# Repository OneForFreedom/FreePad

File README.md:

# This is FreePad.
The revolutonary pad with a 3x5 key matrix layout incorporating 3 rotary encoders!

This is a fully wireless system with a built in Battery! It features a nice!nano as it's main mcu!

I made this because I thought havigng a wireless pad would be really fun to have.

# Juicy Images!
.png)  
.png)  
.png)  
.png)  

# And the BEAUTIFUL BOM!

| Item                 | Price (£) | Price (\$) | Link                                                                           |
| -------------------- | --------- | ---------- | ------------------------------------------------------------------------------ |
| Keycaps              | 3.45      | 4.62       | [Link](https://www.aliexpress.com/item/1005006005905021.html)                  |
| Switches             | 2.59      | 3.47       | [Link](https://www.aliexpress.com/item/1005006578935785.html)                  |
| Nice Nano            | 2.27      | 3.04       | [Link](https://www.aliexpress.com/item/1005001621678794.html)                  |
| Rotary Encoders      | 1.92      | 2.57       | [Link](https://www.aliexpress.com/item/33014968983.html)                       |
| Rotary Encoder Caps  | 1.06      | 1.42       | [Link](https://www.aliexpress.com/item/1005005983134515.html)                  |
| USB-C Cable          | 0.61      | 0.82       | [Link](https://www.aliexpress.com/item/33014968983.html)                       |
| Felt Pads            | 1.95      | 2.61       | [Link](https://www.aliexpress.com/item/1005002289117326.html)                  |
| O Rings              | 1.50      | 2.01       | [Link](https://www.aliexpress.com/item/1005005950575947.html)                  |
| Battery              | 6.39      | 8.56       | [Link](https://www.amazon.co.uk/gp/product/B0C7462TMS?smid=ASLRAS85RTYN3&th=1) |
| 3D Printing Shipping | 3.35      | 4.49       | [Link](https://send.royalmail.com/?iid=RM0624_NAV_SEND)                        |
| PCB                  | 7.94      | 10.64      | [Link](https://jlcpcb.com/)                                                    |
|                      |           |            |                                                                                |
| **Grand Total**      | **33.03** | **44.28**  |                                                                                |

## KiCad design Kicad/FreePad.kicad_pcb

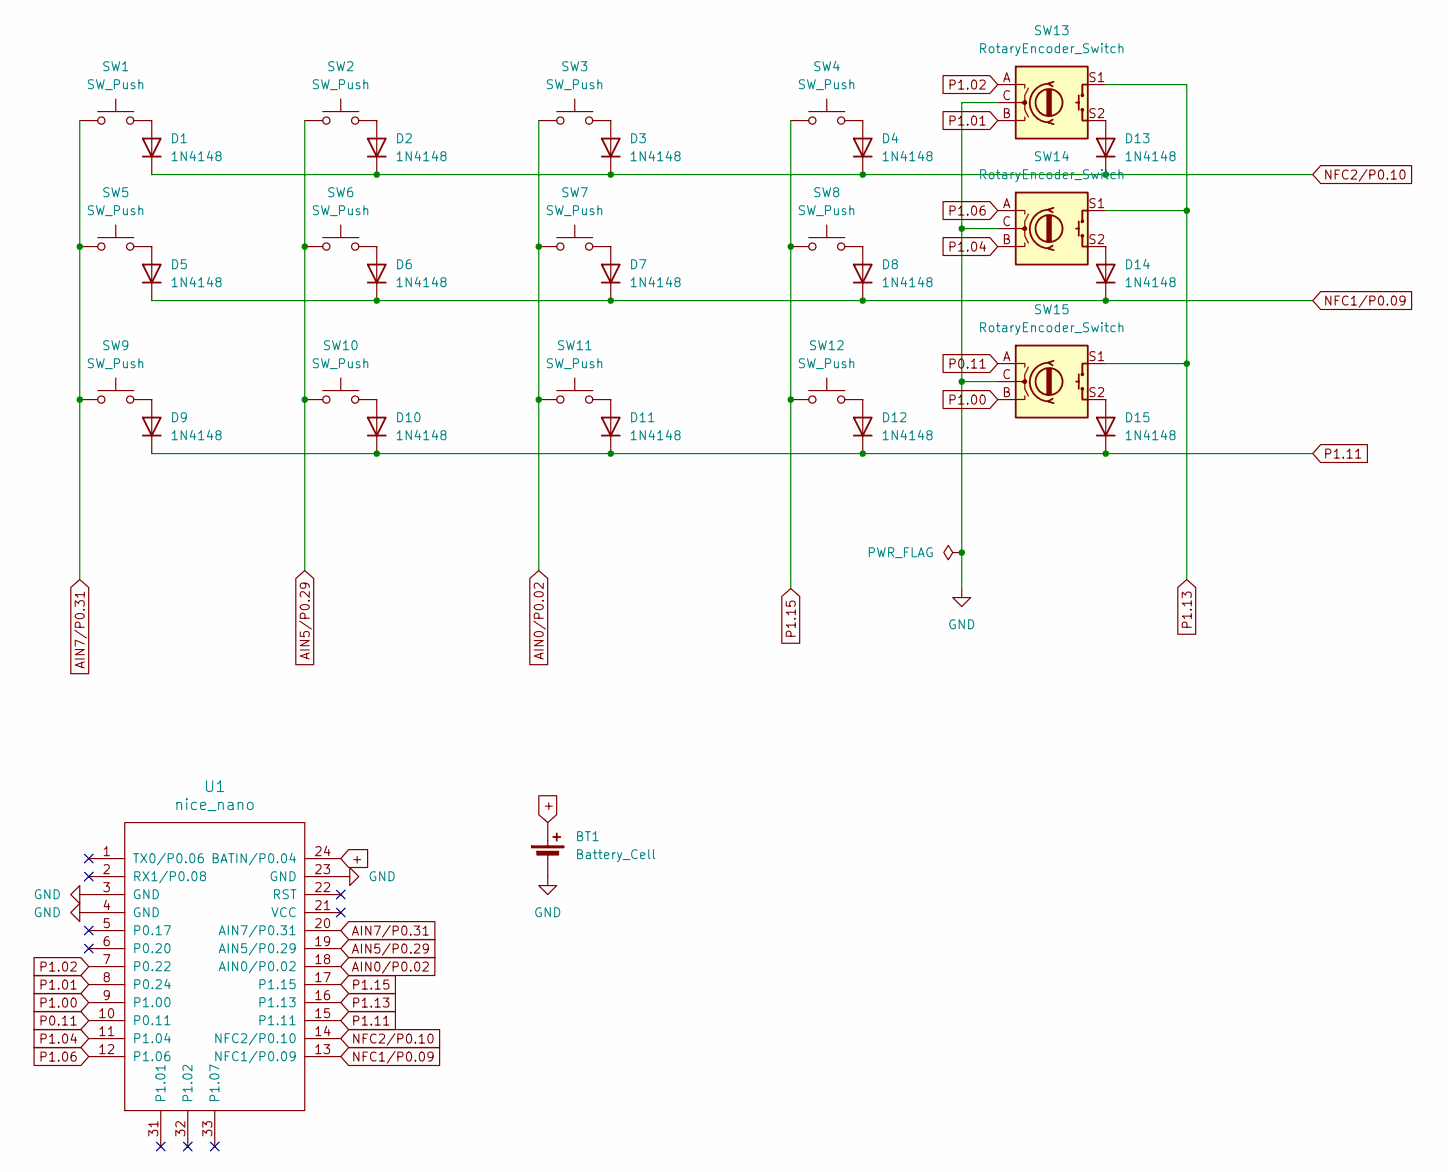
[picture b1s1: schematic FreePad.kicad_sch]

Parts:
BT1: Battery_Cell
D1, D2, D3, D4, D5, D6, D7, D8, D9, D10, D11, D12, D13, D14, D15: 1N4148; D_DO-35_SOD27_P7.62mm_Horizontal
SW1, SW2, SW3, SW4, SW5, SW6, SW7, SW8, SW9, SW10, SW11, SW12: SW_Push; SW_Cherry_MX_1.00u_PCB
SW13, SW14, SW15: RotaryEncoder_Switch; RotaryEncoder_Alps_EC11E-Switch_Vertical_H20mm_MountingHoles
U1: nice_nano

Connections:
+: BT1.1 (+), U1.24 (BATIN/P0.04)
AIN0/P0.02: SW3.1, SW7.1, SW11.1, U1.18 (AIN0/P0.02)
AIN5/P0.29: SW2.1, SW6.1, SW10.1, U1.19 (AIN5/P0.29)
AIN7/P0.31: SW1.1, SW5.1, SW9.1, U1.20 (AIN7/P0.31)
GND: BT1.2 (-), SW13.C, SW14.C, SW15.C, U1.3 (GND), U1.4 (GND), U1.23 (GND)
NFC1/P0.09: D5.1 (K), D6.1 (K), D7.1 (K), D8.1 (K), D14.1 (K), U1.13 (NFC1/P0.09)
NFC2/P0.10: D1.1 (K), D2.1 (K), D3.1 (K), D4.1 (K), D13.1 (K), U1.14 (NFC2/P0.10)
unnamed: D1.2 (A), SW1.2
unnamed: D2.2 (A), SW2.2
unnamed: D3.2 (A), SW3.2
unnamed: D4.2 (A), SW4.2
unnamed: D5.2 (A), SW5.2
unnamed: D6.2 (A), SW6.2
unnamed: D7.2 (A), SW7.2
unnamed: D8.2 (A), SW8.2
unnamed: D9.2 (A), SW9.2
unnamed: D10.2 (A), SW10.2
unnamed: D11.2 (A), SW11.2
unnamed: D12.2 (A), SW12.2
unnamed: D13.2 (A), SW13.S2
unnamed: D14.2 (A), SW14.S2
unnamed: D15.2 (A), SW15.S2
P0.11: SW15.A, U1.10 (P0.11)
P1.00: SW15.B, U1.9 (P1.00)
P1.01: SW13.B, U1.8 (P0.24)
P1.02: SW13.A, U1.7 (P0.22)
P1.04: SW14.B, U1.11 (P1.04)
P1.06: SW14.A, U1.12 (P1.06)
P1.11: D9.1 (K), D10.1 (K), D11.1 (K), D12.1 (K), D15.1 (K), U1.15 (P1.11)
P1.13: SW13.S1, SW14.S1, SW15.S1, U1.16 (P1.13)
P1.15: SW4.1, SW8.1, SW12.1, U1.17 (P1.15)

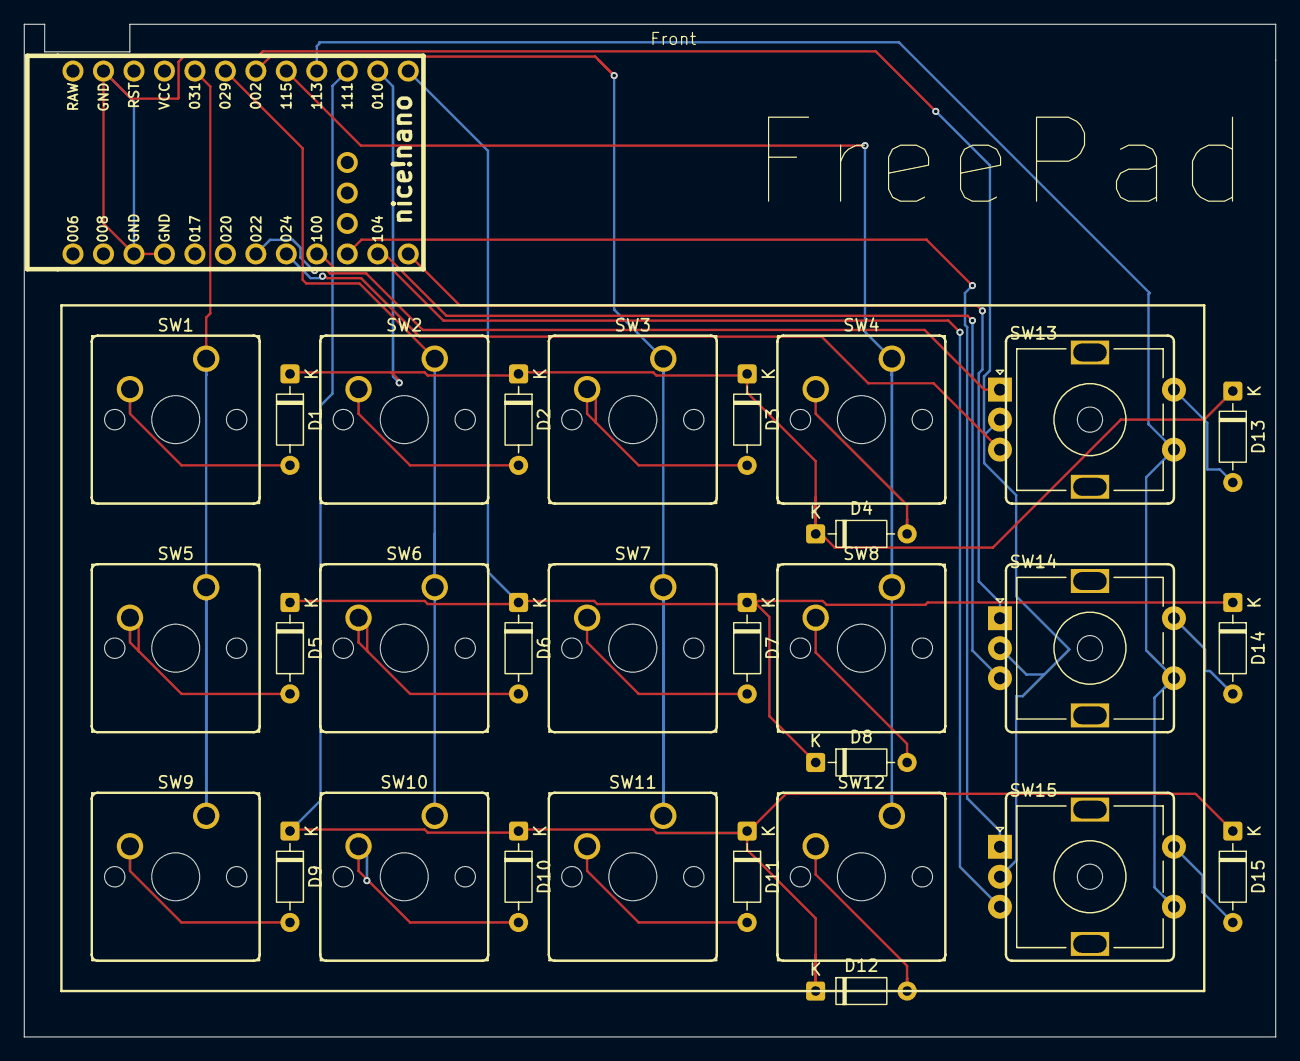
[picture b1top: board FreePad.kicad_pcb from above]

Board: 2 copper layers, 104.3 x 84.4 mm, 31 parts (0 on the bottom side), 30 nets.

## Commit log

2025-07-20 Rename FreePad.zip to Production/FreePad.zip
2025-07-20 Rename FreePad PCB.png to Images/FreePad PCB.png
2025-07-20 Rename FreePad Schematic.png to Images/FreePad Schematic.png
